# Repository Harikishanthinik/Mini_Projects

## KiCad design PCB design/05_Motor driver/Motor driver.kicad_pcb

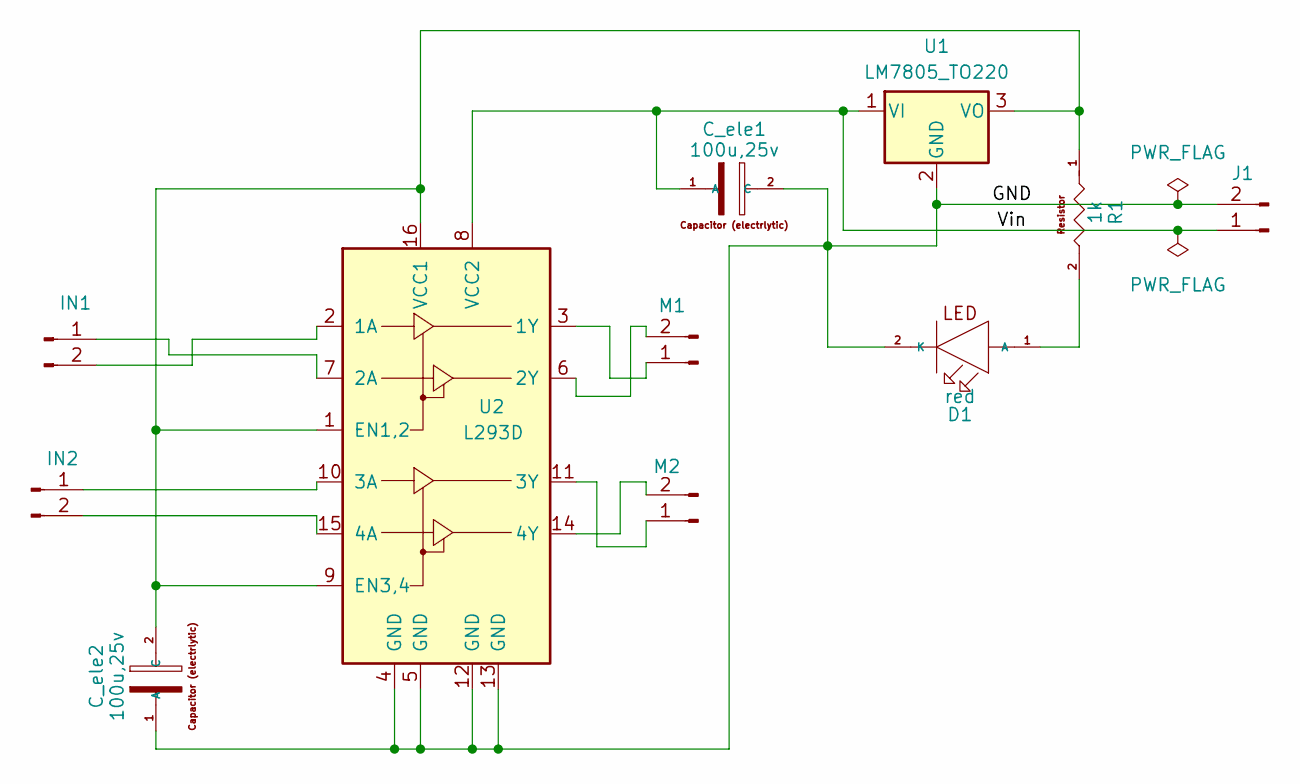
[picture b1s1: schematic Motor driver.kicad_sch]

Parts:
C_ele1, C_ele2: 100u,25v; CP_Radial_D5.0mm_P2.50mm
D1: red; LED_D3.0mm
IN1, IN2: Conn_01x02_Pin; PinHeader_1x02_P2.54mm_Vertical
J1: Conn_01x02_Pin; PinHeader_1x02_P2.54mm_Vertical
M1, M2: Conn_01x02_Pin; TerminalBlock_bornier-2_P5.08mm
R1: 1k; R_Axial_DIN0207_L6.3mm_D2.5mm_P7.62mm_Horizontal
U1: LM7805_TO220; TO-220-3_Vertical
U2: L293D; DIP-16_W7.62mm

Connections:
/GND: C_ele1.2 (C), C_ele2.1 (A), D1.2 (K), J1.2, U1.2 (GND), U2.4 (GND), U2.5 (GND), U2.12 (GND), U2.13 (GND)
/Vin: C_ele1.1 (A), J1.1, U1.1 (VI), U2.8 (VCC2)
unnamed: C_ele2.2 (C), R1.1, U1.3 (VO), U2.1 (EN1,2), U2.9 (EN3,4), U2.16 (VCC1)
unnamed: D1.1 (A), R1.2
unnamed: IN1.1, U2.7 (2A)
unnamed: IN1.2, U2.2 (1A)
unnamed: IN2.1, U2.10 (3A)
unnamed: IN2.2, U2.15 (4A)
unnamed: M1.1, U2.3 (1Y)
unnamed: M1.2, U2.6 (2Y)
unnamed: M2.1, U2.11 (3Y)
unnamed: M2.2, U2.14 (4Y)

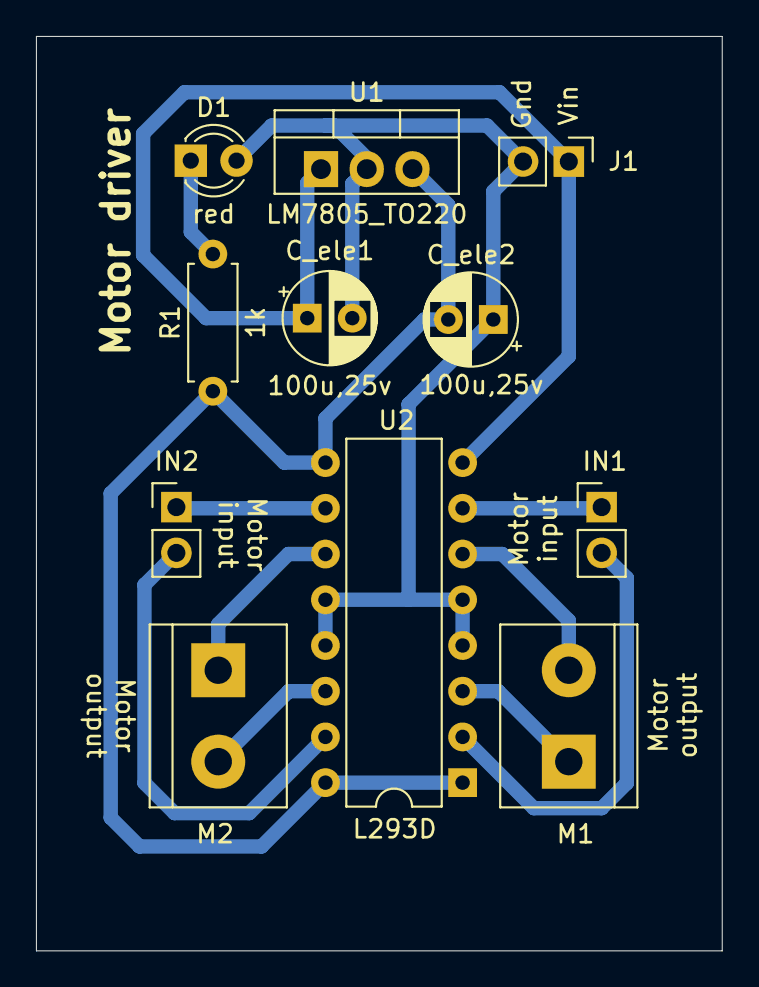
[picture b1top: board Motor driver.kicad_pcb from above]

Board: 2 copper layers, 38.1 x 50.8 mm, 11 parts (0 on the bottom side), 12 nets.

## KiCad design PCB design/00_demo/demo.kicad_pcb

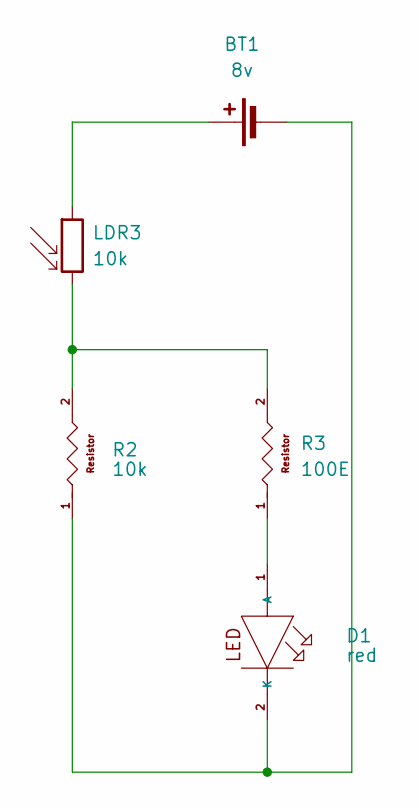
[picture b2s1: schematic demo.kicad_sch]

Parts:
BT1: 8v; TerminalBlock_bornier-2_P5.08mm
D1: red; Led_D5.00mm
LDR3: 10k; R_LDR_10x8.5mm_P7.6mm_Vertical
R2: 10k; R_D1.6mm
R3: 100E; R_D1.6mm

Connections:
unnamed: BT1.1 (+), LDR3.1
unnamed: BT1.2 (-), D1.2 (K), R2.1
unnamed: D1.1 (A), R3.1
unnamed: LDR3.2, R2.2, R3.2

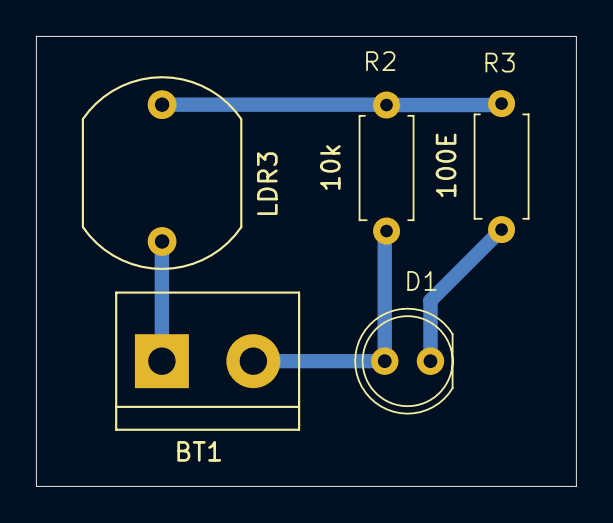
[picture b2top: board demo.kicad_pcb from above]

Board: 2 copper layers, 30.0 x 25.0 mm, 5 parts (0 on the bottom side), 4 nets.

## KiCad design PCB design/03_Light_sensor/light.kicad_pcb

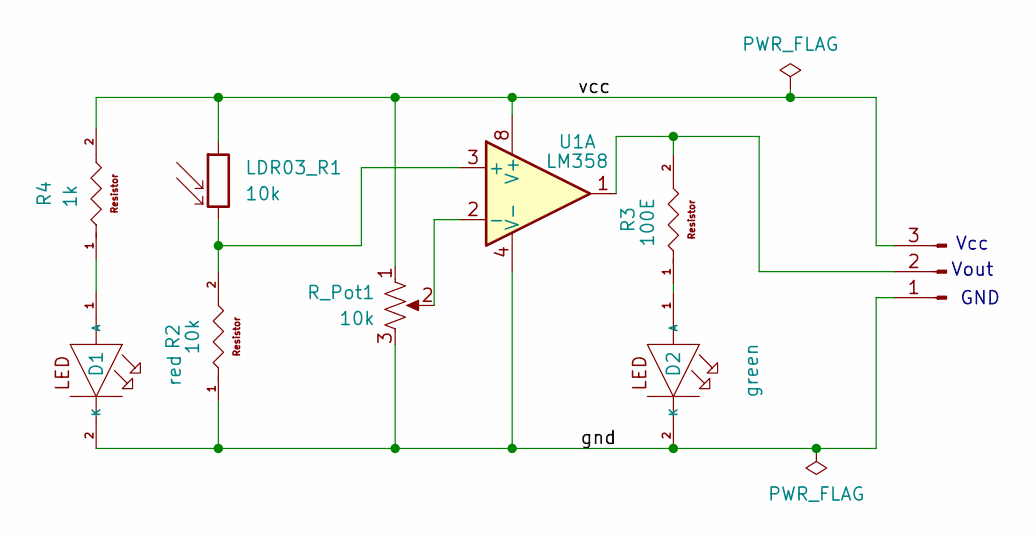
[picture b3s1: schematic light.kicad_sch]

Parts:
D1: red; Led_D5.00mm
D2: green; Led_D5.00mm
J1: Conn_01x03_Pin; PinHeader_1x03_P2.54mm_Vertical
LDR03_R1: 10k; R_LDR_10x8.5mm_P7.6mm_Vertical
R2: 10k; R_Axial_DIN0207_L6.3mm_D2.5mm_P7.62mm_Horizontal
R3: 100E; R_Axial_DIN0207_L6.3mm_D2.5mm_P7.62mm_Horizontal
R4: 1k; R_Axial_DIN0207_L6.3mm_D2.5mm_P7.62mm_Horizontal
R_Pot1: 10k; Potentiometer_Runtron_RM-065_Vertical
U1: LM358; DIP-8_W7.62mm

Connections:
/gnd: D1.2 (K), D2.2 (K), J1.1, R2.1, R_Pot1.3, U1.4 (V-)
/vcc: J1.3, LDR03_R1.1, R4.2, R_Pot1.1, U1.8 (V+)
unnamed: D1.1 (A), R4.1
unnamed: D2.1 (A), R3.1
unnamed: J1.2, R3.2, U1.1
unnamed: LDR03_R1.2, R2.2, U1.3 (+)
unnamed: R_Pot1.2, U1.2 (-)

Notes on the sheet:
GND
Vcc
Vout

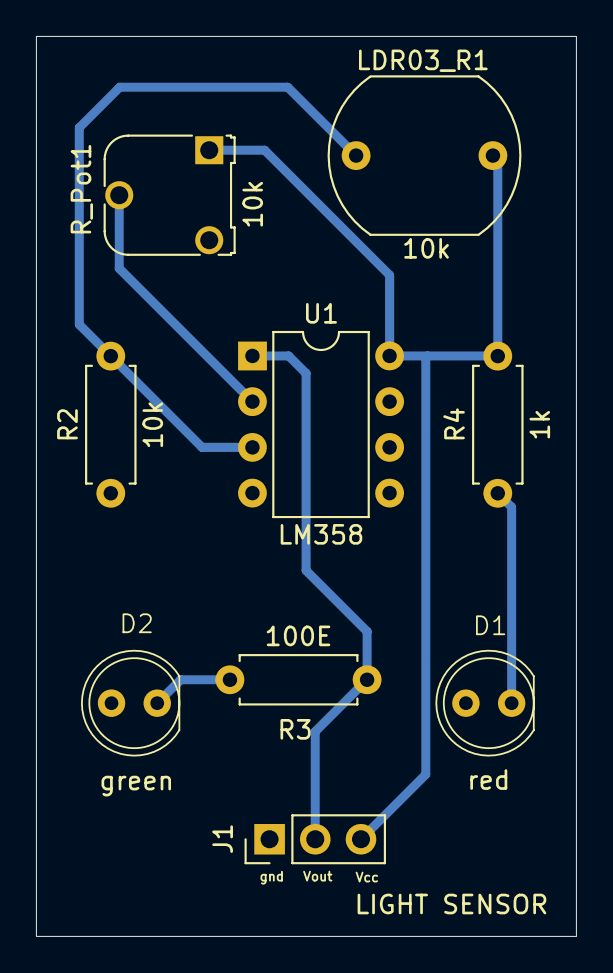
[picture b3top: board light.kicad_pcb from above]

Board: 2 copper layers, 30.0 x 50.0 mm, 9 parts (0 on the bottom side), 7 nets.

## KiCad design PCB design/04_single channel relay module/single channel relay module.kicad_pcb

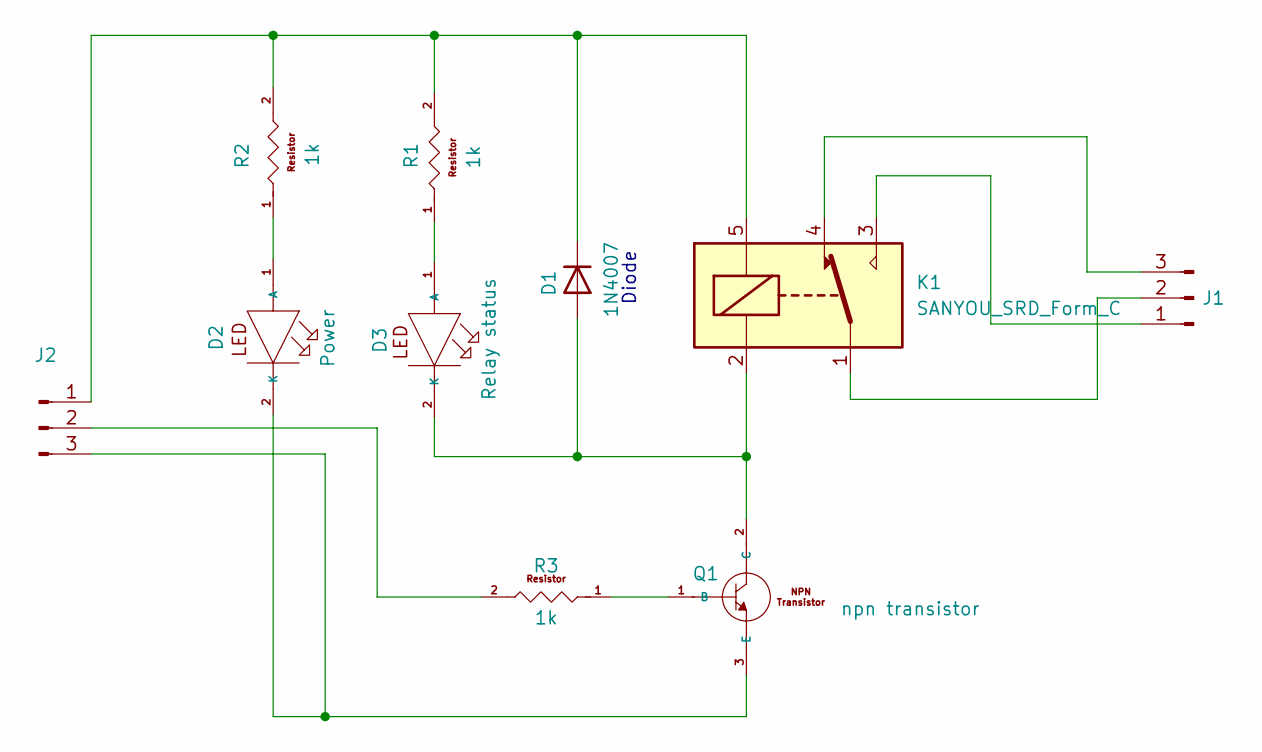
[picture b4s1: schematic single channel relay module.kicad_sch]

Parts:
D1: 1N4007; D_DO-41_SOD81_P7.62mm_Horizontal
D2: Power; LED_D3.0mm
D3: Relay status; LED_D3.0mm
J1: Conn_01x03_Pin; TerminalBlock_bornier-3_P5.08mm
J2: Conn_01x03_Pin; PinHeader_1x03_P2.00mm_Vertical
K1: SANYOU_SRD_Form_C; Relay_SPDT_SANYOU_SRD_Series_Form_C
Q1: npn transistor; TO-92_Inline_Wide
R1, R2, R3: 1k; R_Axial_DIN0207_L6.3mm_D2.5mm_P7.62mm_Horizontal

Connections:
unnamed: D1.2 (A), D3.2 (K), K1.2, Q1.2 (C)
unnamed: D1.1 (K), J2.1, K1.5, R1.2, R2.2
unnamed: D2.1 (A), R2.1
unnamed: D2.2 (K), J2.3, Q1.3 (E)
unnamed: D3.1 (A), R1.1
unnamed: J1.1, K1.3
unnamed: J1.2, K1.1
unnamed: J1.3, K1.4
unnamed: J2.2, R3.2
unnamed: Q1.1 (B), R3.1

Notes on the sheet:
Diode

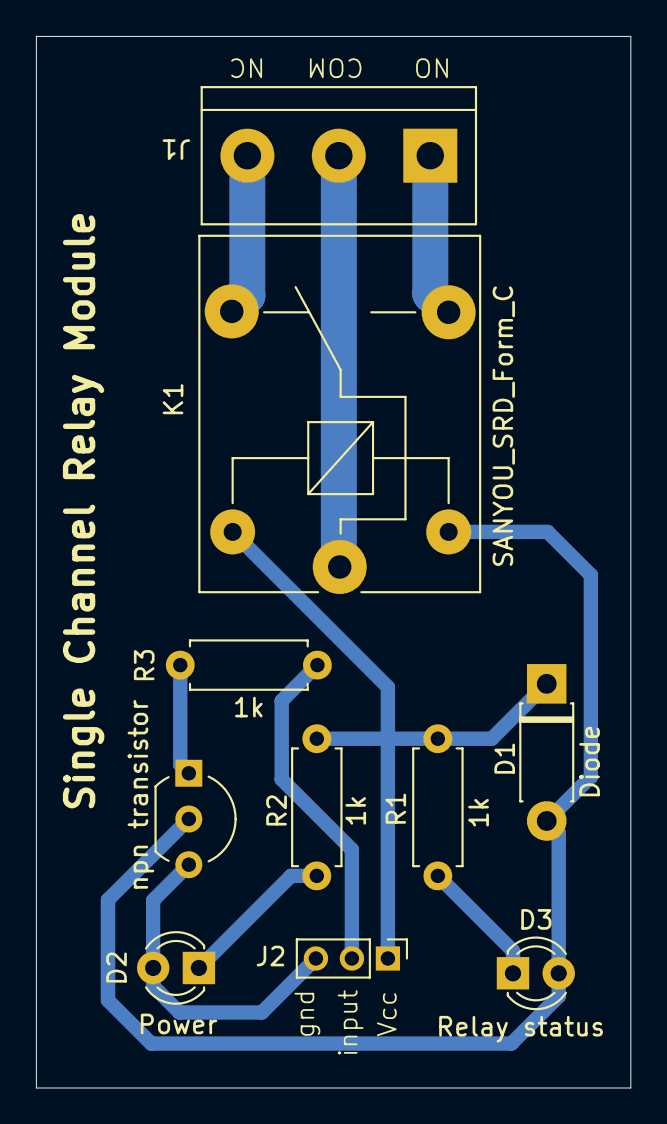
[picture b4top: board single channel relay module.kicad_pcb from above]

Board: 2 copper layers, 33.0 x 58.4 mm, 10 parts (0 on the bottom side), 10 nets.

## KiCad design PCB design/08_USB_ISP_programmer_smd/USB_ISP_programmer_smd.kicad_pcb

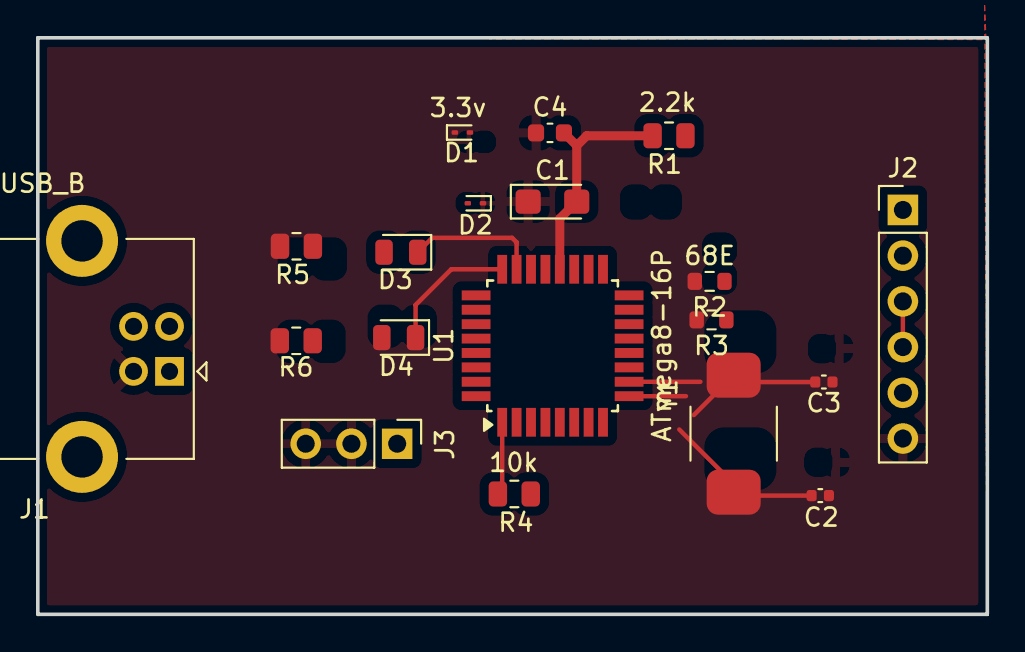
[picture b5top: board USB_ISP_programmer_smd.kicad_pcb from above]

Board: 2 copper layers, 52.8 x 32.0 mm, 19 parts (0 on the bottom side), 18 nets.

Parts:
C1: 4.7u; CP_EIA-3216-18_Kemet-A
C2, C3: 22n; C_0402_1005Metric
C4: 100n; C_0603_1608Metric
D1, D2: 3.3v; D_SOD-923
D3: LED_R; LED_0805_2012Metric
D4: LED_G; LED_0805_2012Metric
J1: USB_B; USB_B_Lumberg_2411_02_Horizontal
J2: Conn_01x06_Pin; PinHeader_1x06_P2.54mm_Vertical
J3: Conn_01x03_Pin; PinHeader_1x03_P2.54mm_Vertical
R1: 2.2k; R_0805_2012Metric
R2, R3: 68E; R_0603_1608Metric
R4: 10k; R_0805_2012Metric
R5, R6: 1k; R_0805_2012Metric
U1: ATmega8-16P; TQFP-32_7x7mm_P0.8mm
Y1: xtl; Crystal_SMD_TXC_AX_8045-2Pin_8.0x4.5mm

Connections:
/Gnd: C1.1 (A), C2.1, C3.1, C4.1, D1.1 (K), D2.1 (K), J1.4 (GND), J2.6, J3.2, J3.3, U1.22 (AGND)
/Vcc: C1.2 (C), C4.2, J1.1 (VBUS), J2.1, R1.2, R4.2, R5.2, R6.2, U1.20 (AVCC)
unnamed: D1.2 (A), J1.3 (D+), R2.1
unnamed: D2.2 (A), J1.2 (D-), R1.1, R3.1
unnamed: D3.2 (A), R5.1
unnamed: D3.1 (K), U1.23 (PC0)
unnamed: D4.2 (A), R6.1
unnamed: D4.1 (K), U1.24 (PC1)
unnamed: J2.2, U1.19 (PB5)
unnamed: J2.3, U1.17 (PB3)
unnamed: J2.4, U1.18 (PB4)
unnamed: J2.5, U1.16 (PB2)
unnamed: J3.1, U1.25 (PC2)
unnamed: R3.2, U1.14 (PB0)
unnamed: R2.2, U1.4 (PD2), U1.15 (PB1)
unnamed: C2.2, U1.9 (PB6/XTAL1), Y1.2
unnamed: C3.2, U1.10 (PB7/XTAL2), Y1.1
unnamed: R4.1, U1.1 (PC6/~RESET)

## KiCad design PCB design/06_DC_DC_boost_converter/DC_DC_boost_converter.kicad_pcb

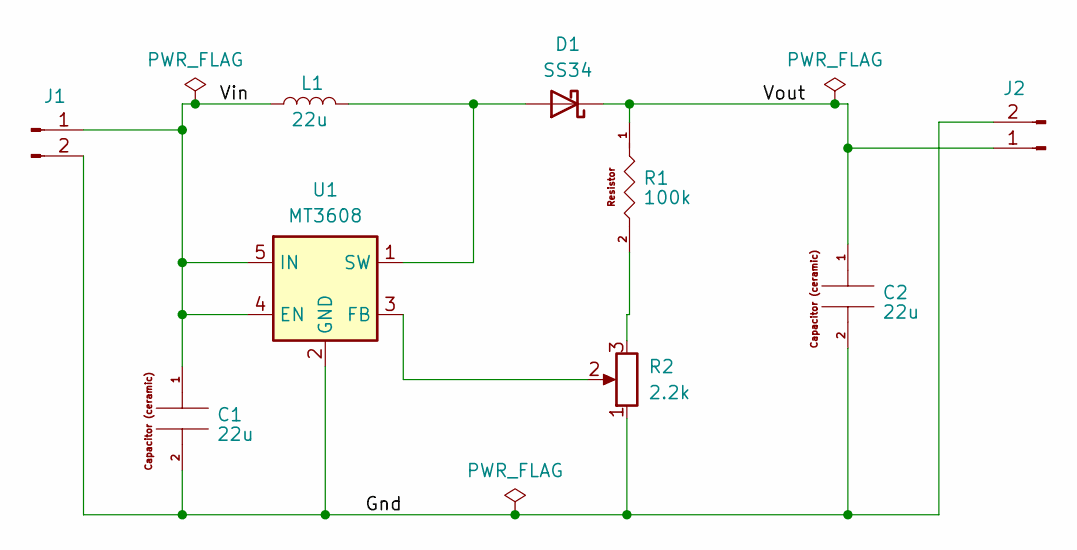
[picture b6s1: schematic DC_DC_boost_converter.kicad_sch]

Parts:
C1, C2: 22u; CP_Elec_5x4.5
D1: SS34; D_SMA
J1, J2: Conn_01x02_Pin; PinHeader_1x02_P2.54mm_Vertical
L1: 22u; L_KOHERelec_MDA5030
R1: 100k; R_1206_3216Metric_Pad1.30x1.75mm_HandSolder
R2: 2.2k; Potentiometer_Bourns_3314G_Vertical
U1: MT3608; SOT-23-6

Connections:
/Gnd: C1.2, C2.2, J1.2, J2.2, R2.1, U1.2 (GND)
/Vin: C1.1, J1.1, L1.2, U1.4 (EN), U1.5 (IN)
/Vout: C2.1, D1.1 (K), J2.1, R1.1
unnamed: D1.2 (A), L1.1, U1.1 (SW)
unnamed: R1.2, R2.3
unnamed: R2.2, U1.3 (FB)

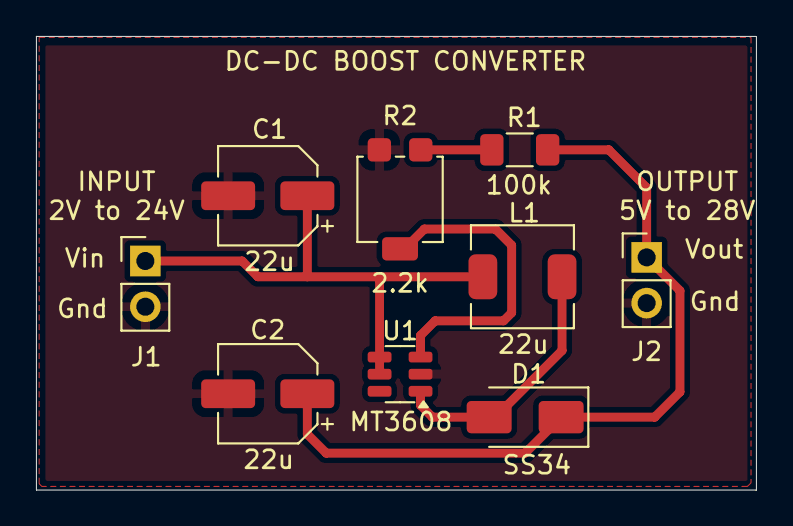
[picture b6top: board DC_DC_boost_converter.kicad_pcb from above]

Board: 2 copper layers, 40.0 x 25.2 mm, 9 parts (0 on the bottom side), 6 nets.

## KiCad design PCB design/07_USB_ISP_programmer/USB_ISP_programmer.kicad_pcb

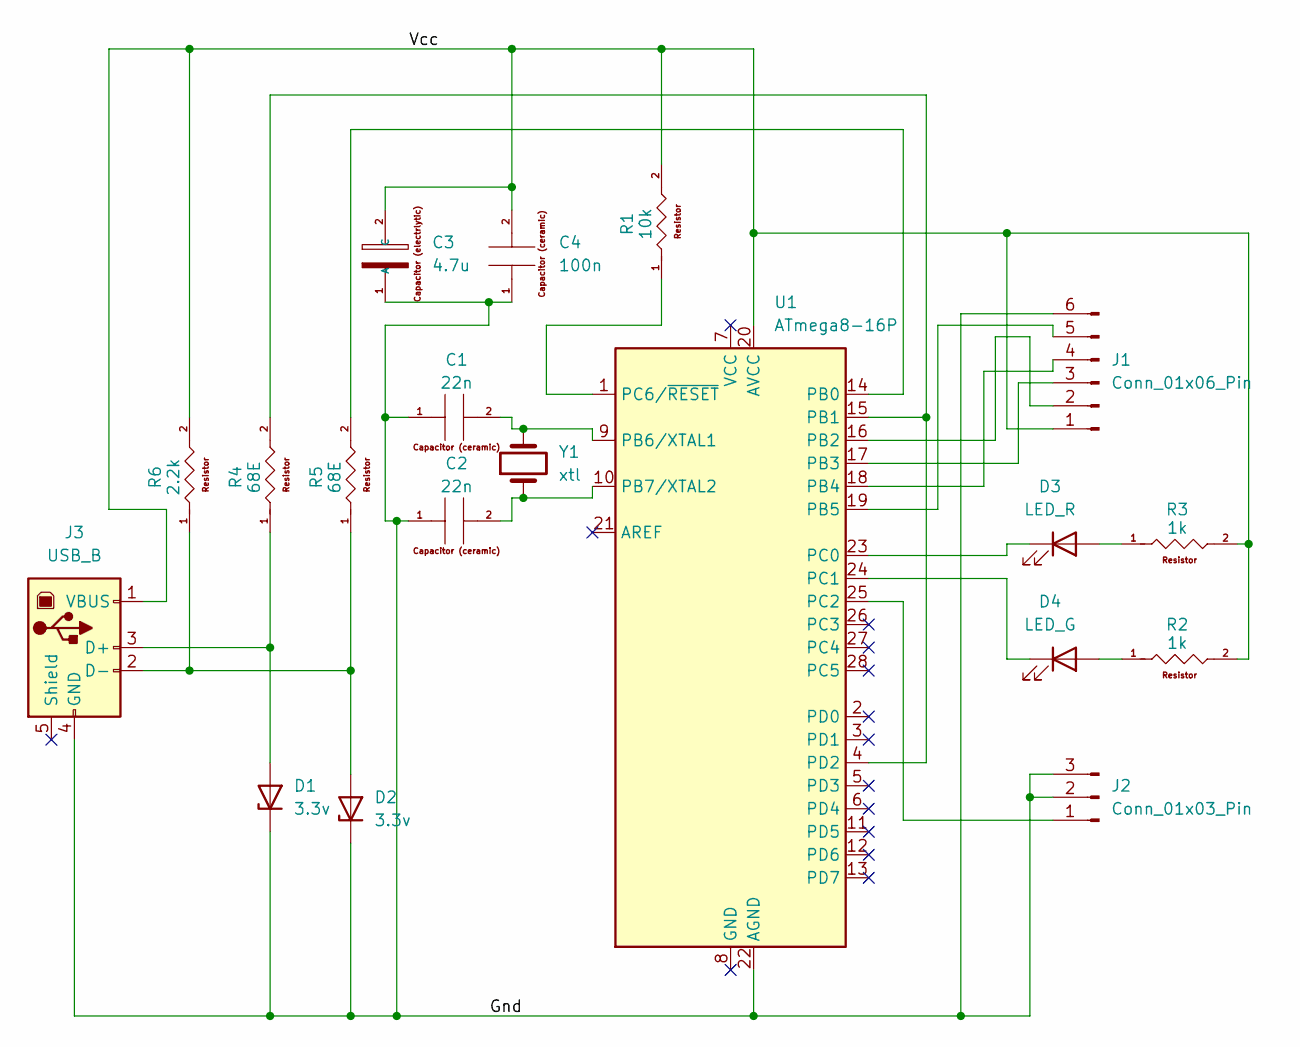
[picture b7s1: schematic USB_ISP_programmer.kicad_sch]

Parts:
C1, C2: 22n; C_Disc_D5.0mm_W2.5mm_P2.50mm
C3: 4.7u; CP_Radial_D5.0mm_P2.50mm
C4: 100n; C_Disc_D5.0mm_W2.5mm_P2.50mm
D1, D2: 3.3v; D_DO-41_SOD81_P7.62mm_Horizontal
D3: LED_R; LED_D3.0mm
D4: LED_G; LED_D3.0mm
J1: Conn_01x06_Pin; PinHeader_1x06_P2.54mm_Vertical
J2: Conn_01x03_Pin; PinHeader_1x03_P2.54mm_Vertical
J3: USB_B; USB_B_Lumberg_2411_02_Horizontal
R1: 10k; R_Axial_DIN0207_L6.3mm_D2.5mm_P7.62mm_Horizontal
R2, R3: 1k; R_Axial_DIN0207_L6.3mm_D2.5mm_P7.62mm_Horizontal
R4, R5: 68E; R_Axial_DIN0207_L6.3mm_D2.5mm_P7.62mm_Horizontal
R6: 2.2k; R_Axial_DIN0207_L6.3mm_D2.5mm_P7.62mm_Horizontal
U1: ATmega8-16P; DIP-28_W7.62mm
Y1: xtl; Crystal_HC49-4H_Vertical

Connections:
/Gnd: C1.1, C2.1, C3.1 (A), C4.1, D1.1 (K), D2.1 (K), J1.6, J2.2, J2.3, J3.4 (GND), U1.22 (AGND)
/Vcc: C3.2 (C), C4.2, J1.1, J3.1 (VBUS), R1.2, R2.2, R3.2, R6.2, U1.20 (AVCC)
unnamed: D1.2 (A), J3.3 (D+), R4.1
unnamed: D2.2 (A), J3.2 (D-), R5.1, R6.1
unnamed: D3.2 (A), R3.1
unnamed: D3.1 (K), U1.23 (PC0)
unnamed: D4.2 (A), R2.1
unnamed: D4.1 (K), U1.24 (PC1)
unnamed: J1.2, U1.16 (PB2)
unnamed: J1.3, U1.17 (PB3)
unnamed: J1.4, U1.18 (PB4)
unnamed: J1.5, U1.19 (PB5)
unnamed: J2.1, U1.25 (PC2)
unnamed: R5.2, U1.14 (PB0)
unnamed: R4.2, U1.4 (PD2), U1.15 (PB1)
unnamed: C1.2, U1.9 (PB6/XTAL1), Y1.2
unnamed: C2.2, U1.10 (PB7/XTAL2), Y1.1
unnamed: R1.1, U1.1 (PC6/~RESET)

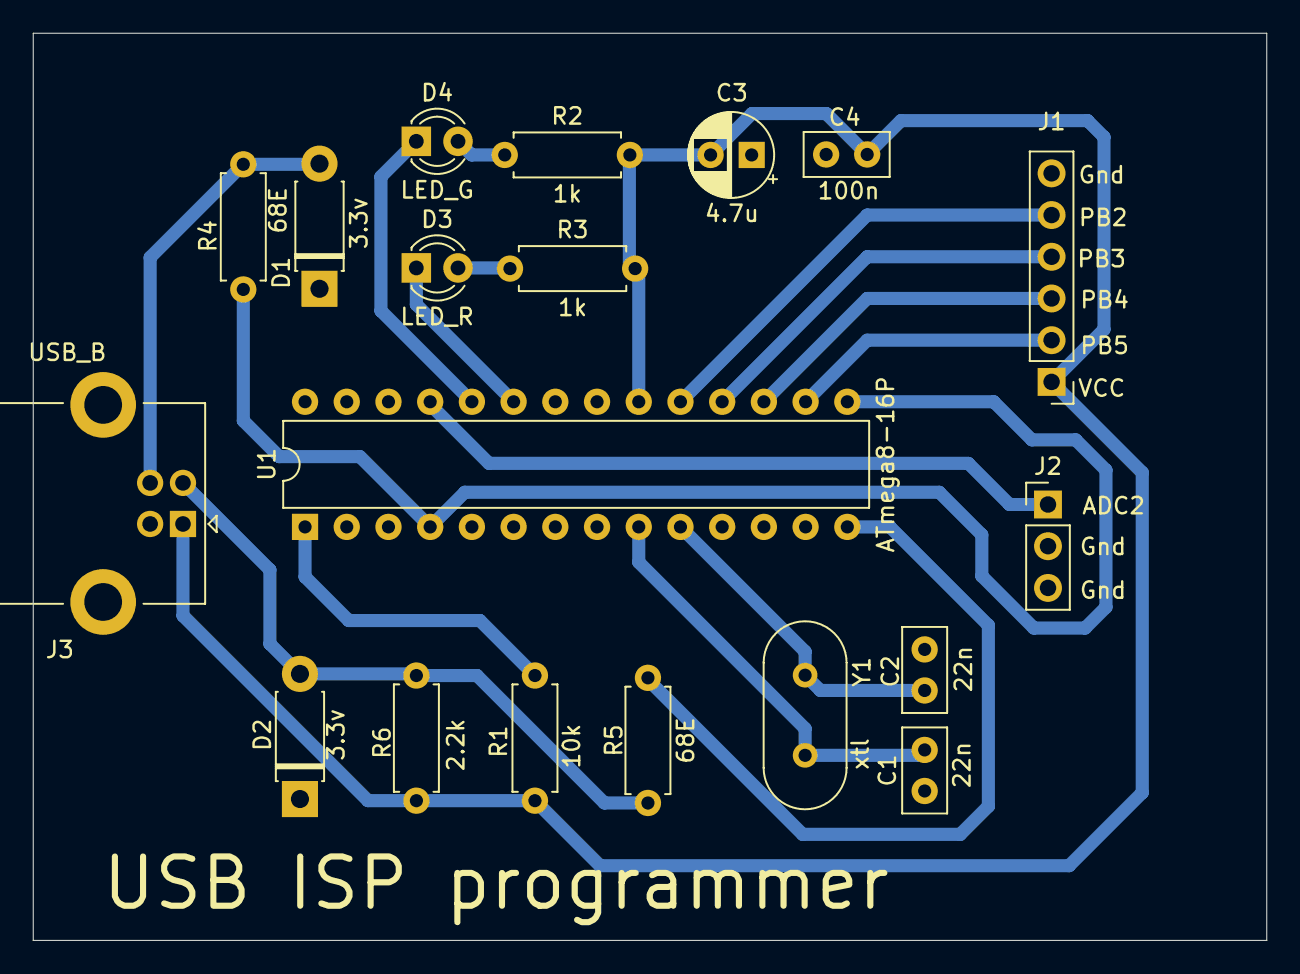
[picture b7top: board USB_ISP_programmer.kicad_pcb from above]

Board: 2 copper layers, 75.1 x 55.2 mm, 19 parts (0 on the bottom side), 18 nets.
